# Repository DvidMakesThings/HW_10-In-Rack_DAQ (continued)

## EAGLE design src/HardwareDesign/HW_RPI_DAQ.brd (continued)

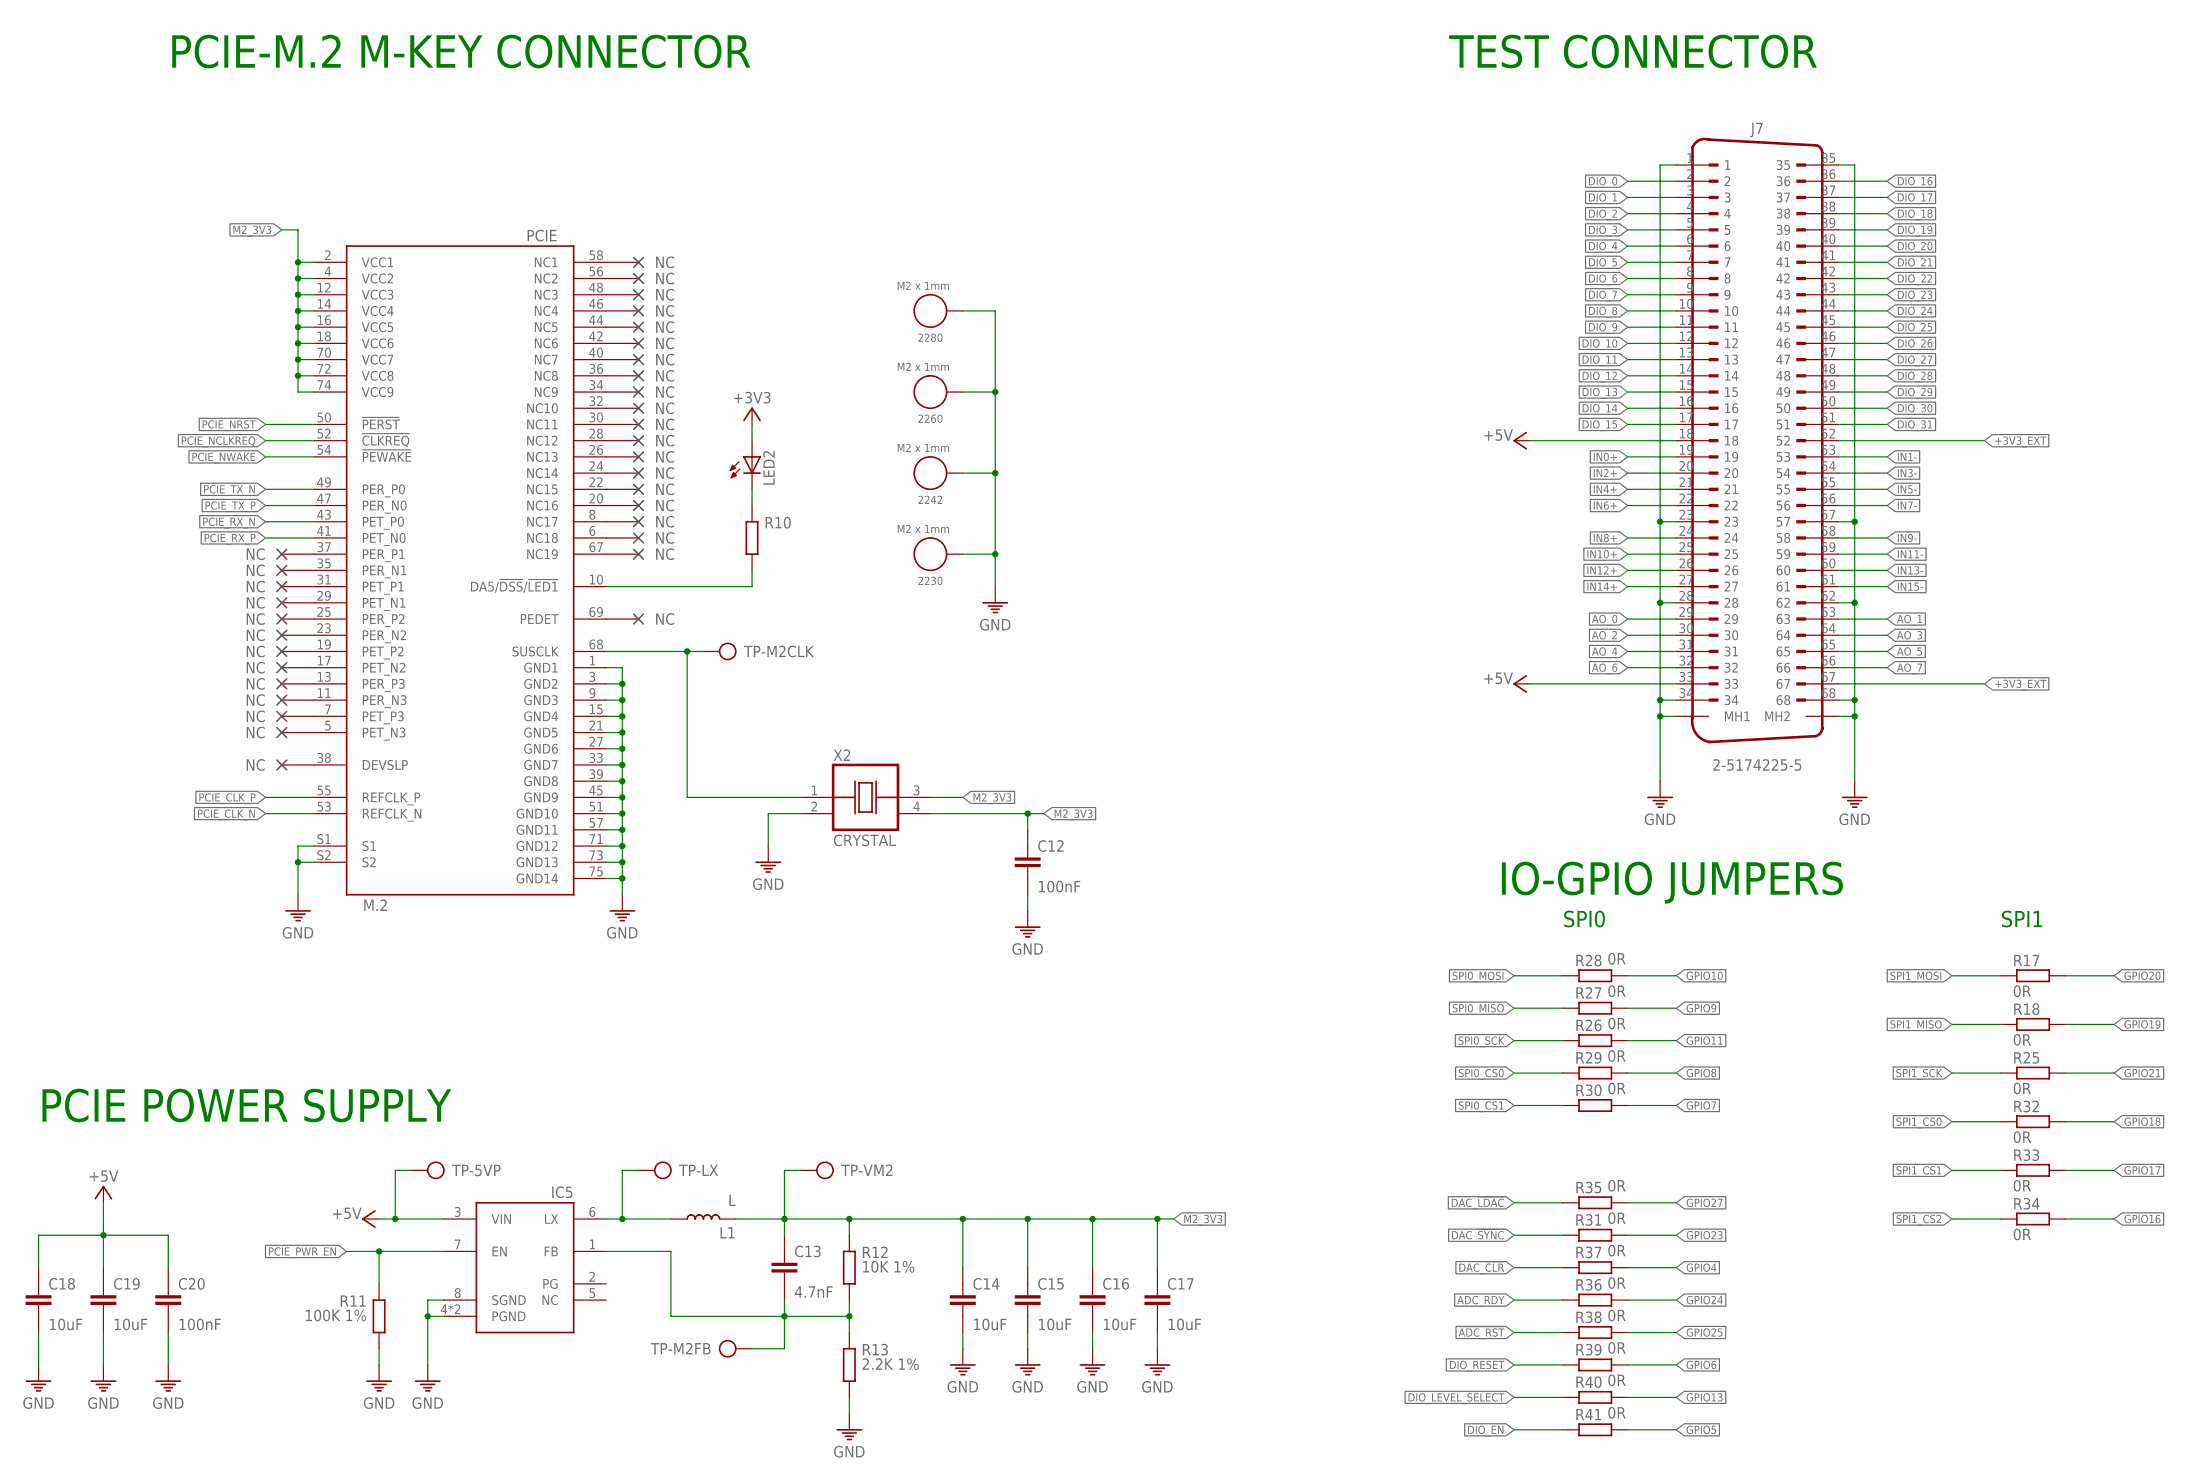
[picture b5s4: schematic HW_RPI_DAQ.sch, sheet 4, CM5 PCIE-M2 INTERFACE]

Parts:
2230, 2242, 2260, 2280: M2 x 1mm; WA-SMSI_9774010243
C12, C20: 100nF; 0402
C13: 4.7nF; 0402
C14, C15, C16, C17, C18, C19: 10uF; 0805
IC5: AP3441SHE-7B; SON50P201X201X56-9T90X170N
J7: 2-5174225-5
L1: L; SRR5228A
LED2: LEDCHIPLED_0805; CHIPLED_0805
PCIE: M.2
R10: R0402; 0402
R11: 100K 1%; 0402
R12: 10K 1%; 0402
R13: 2.2K 1%; 0402
R17, R18, R25, R26, R27, R28, R29, R30, R31, R32, R33, R34, R35, R36, R37, R38, R39, R40, R41: 0R; 0603
TP-5VP: TP
TP-LX: TP
TP-M2CLK, TP-M2FB: TP
TP-VM2: TP
X2: CRYSTAL; OSCCC500X320X130

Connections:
!ADC_RST: R38.1; also elsewhere on the board
+3V3: LED2.A; also elsewhere on the board
+3V3_EXT: J7.52, J7.67; also elsewhere on the board
+5V: C18.1, C19.1, C20.1, IC5.3 (VIN), J7.18, J7.33, TP-5VP.TP; also elsewhere on the board
ADC_RDY: R36.1; also elsewhere on the board
AO_0: J7.29; also elsewhere on the board
AO_1: J7.63; also elsewhere on the board
AO_2: J7.30; also elsewhere on the board
AO_3: J7.64; also elsewhere on the board
AO_4: J7.31; also elsewhere on the board
AO_5: J7.65; also elsewhere on the board
AO_6: J7.32; also elsewhere on the board
AO_7: J7.66; also elsewhere on the board
DAC_!CLR: R37.1; also elsewhere on the board
DAC_!LDAC: R35.1; also elsewhere on the board
DAC_!SYNC: R31.1; also elsewhere on the board
DIO_0: J7.2; also elsewhere on the board
DIO_1: J7.3; also elsewhere on the board
DIO_2: J7.4; also elsewhere on the board
DIO_3: J7.5; also elsewhere on the board
DIO_4: J7.6; also elsewhere on the board
DIO_5: J7.7; also elsewhere on the board
DIO_6: J7.8; also elsewhere on the board
DIO_7: J7.9; also elsewhere on the board
DIO_8: J7.10; also elsewhere on the board
DIO_9: J7.11; also elsewhere on the board
DIO_10: J7.12; also elsewhere on the board
DIO_11: J7.13; also elsewhere on the board
DIO_12: J7.14; also elsewhere on the board
DIO_13: J7.15; also elsewhere on the board
DIO_14: J7.16; also elsewhere on the board
DIO_15: J7.17; also elsewhere on the board
DIO_16: J7.36; also elsewhere on the board
DIO_17: J7.37; also elsewhere on the board
DIO_18: J7.38; also elsewhere on the board
DIO_19: J7.39; also elsewhere on the board
DIO_20: J7.40; also elsewhere on the board
DIO_21: J7.41; also elsewhere on the board
DIO_22: J7.42; also elsewhere on the board
DIO_23: J7.43; also elsewhere on the board
DIO_24: J7.44; also elsewhere on the board
DIO_25: J7.45; also elsewhere on the board
DIO_26: J7.46; also elsewhere on the board
DIO_27: J7.47; also elsewhere on the board
DIO_28: J7.48; also elsewhere on the board
DIO_29: J7.49; also elsewhere on the board
DIO_30: J7.50; also elsewhere on the board
DIO_31: J7.51; also elsewhere on the board
DIO_EN: R41.1; also elsewhere on the board
DIO_LEVEL_SELECT: R40.1; also elsewhere on the board
DIO_RESET: R39.1; also elsewhere on the board
GND: 2230.1, 2242.1, 2260.1, 2280.1, C12.2, C14.2, C15.2, C16.2, C17.2, C18.2, C19.2, C20.2, IC5.4 (PGND), IC5.8 (SGND), IC5.9 (PGND), J7.1, J7.23, J7.28, J7.34, J7.35, J7.57, J7.62, J7.68, J7.MH1, J7.MH2, PCIE.1 (GND1), PCIE.3 (GND2), PCIE.9 (GND3), PCIE.15 (GND4), PCIE.21 (GND5), PCIE.27 (GND6), PCIE.33 (GND7), PCIE.39 (GND8), PCIE.45 (GND9), PCIE.51 (GND10), PCIE.57 (GND11), PCIE.71 (GND12), PCIE.73 (GND13), PCIE.75 (GND14), PCIE.S1, PCIE.S2, R11.2, R13.2, X2.2 (VSS); also elsewhere on the board
GPIO4: R37.2; also elsewhere on the board
GPIO5: R41.2; also elsewhere on the board
GPIO6: R39.2; also elsewhere on the board
GPIO7: R30.2; also elsewhere on the board
GPIO8: R29.2; also elsewhere on the board
GPIO9: R27.2; also elsewhere on the board
GPIO10: R28.2; also elsewhere on the board
GPIO11: R26.2; also elsewhere on the board
GPIO13: R40.2; also elsewhere on the board
GPIO16: R34.2; also elsewhere on the board
GPIO17: R33.2; also elsewhere on the board
GPIO18: R32.2; also elsewhere on the board
GPIO19: R18.2; also elsewhere on the board
GPIO20: R17.2; also elsewhere on the board
GPIO21: R25.2; also elsewhere on the board
GPIO23: R31.2; also elsewhere on the board
GPIO24: R36.2; also elsewhere on the board
GPIO25: R38.2; also elsewhere on the board
GPIO27: R35.2; also elsewhere on the board
IN0+: J7.19; also elsewhere on the board
IN1-: J7.53; also elsewhere on the board
IN2+: J7.20; also elsewhere on the board
IN3-: J7.54; also elsewhere on the board
IN4+: J7.21; also elsewhere on the board
IN5-: J7.55; also elsewhere on the board
IN6+: J7.22; also elsewhere on the board
IN7-: J7.56; also elsewhere on the board
IN8+: J7.24; also elsewhere on the board
IN9-: J7.58; also elsewhere on the board
IN10+: J7.25; also elsewhere on the board
IN11-: J7.59; also elsewhere on the board
IN12+: J7.26; also elsewhere on the board
IN13-: J7.60; also elsewhere on the board
IN14+: J7.27; also elsewhere on the board
IN15-: J7.61; also elsewhere on the board
M2_3V3: C12.1, C13.1, C14.1, C15.1, C16.1, C17.1, L1.2, PCIE.2 (VCC1), PCIE.4 (VCC2), PCIE.12 (VCC3), PCIE.14 (VCC4), PCIE.16 (VCC5), PCIE.18 (VCC6), PCIE.70 (VCC7), PCIE.72 (VCC8), PCIE.74 (VCC9), R12.1, TP-VM2.TP, X2.3 (OUT), X2.4 (VDD)
unnamed: PCIE.10 (DA5/!DSS!/!LED1), R10.2
unnamed: LED2.C, R10.1
unnamed: IC5.6 (LX), L1.1, TP-LX.TP
unnamed: C13.2, IC5.1 (FB), R12.2, R13.1, TP-M2FB.TP
unnamed: PCIE.68 (SUSCLK), TP-M2CLK.TP, X2.1 (CON)
PCIE_CLK_N: PCIE.53 (REFCLK_N); also elsewhere on the board
PCIE_CLK_P: PCIE.55 (REFCLK_P); also elsewhere on the board
PCIE_NCLKREQ: PCIE.52 (!CLKREQ); also elsewhere on the board
PCIE_NRST: PCIE.50 (!PERST); also elsewhere on the board
PCIE_NWAKE: PCIE.54 (!PEWAKE); also elsewhere on the board
PCIE_PWR_EN: IC5.7 (EN), R11.1; also elsewhere on the board
PCIE_RX_N: PCIE.43 (PET_P0); also elsewhere on the board
PCIE_RX_P: PCIE.41 (PET_N0); also elsewhere on the board
PCIE_TX_N: PCIE.49 (PER_P0); also elsewhere on the board
PCIE_TX_P: PCIE.47 (PER_N0); also elsewhere on the board
SPI0_CS0: R29.1; also elsewhere on the board
SPI0_CS1: R30.1; also elsewhere on the board
SPI0_MISO: R27.1; also elsewhere on the board
SPI0_MOSI: R28.1; also elsewhere on the board
SPI0_SCK: R26.1; also elsewhere on the board
SPI1_CS0: R32.1; also elsewhere on the board
SPI1_CS1: R33.1; also elsewhere on the board
SPI1_CS2: R34.1; also elsewhere on the board
SPI1_MISO: R18.1; also elsewhere on the board
SPI1_MOSI: R17.1; also elsewhere on the board
SPI1_SCK: R25.1; also elsewhere on the board

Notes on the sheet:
PCIE-M.2 M-KEY CONNECTOR
PCIE POWER SUPPLY
TEST CONNECTOR
IO-GPIO JUMPERS
SPI0
SPI1

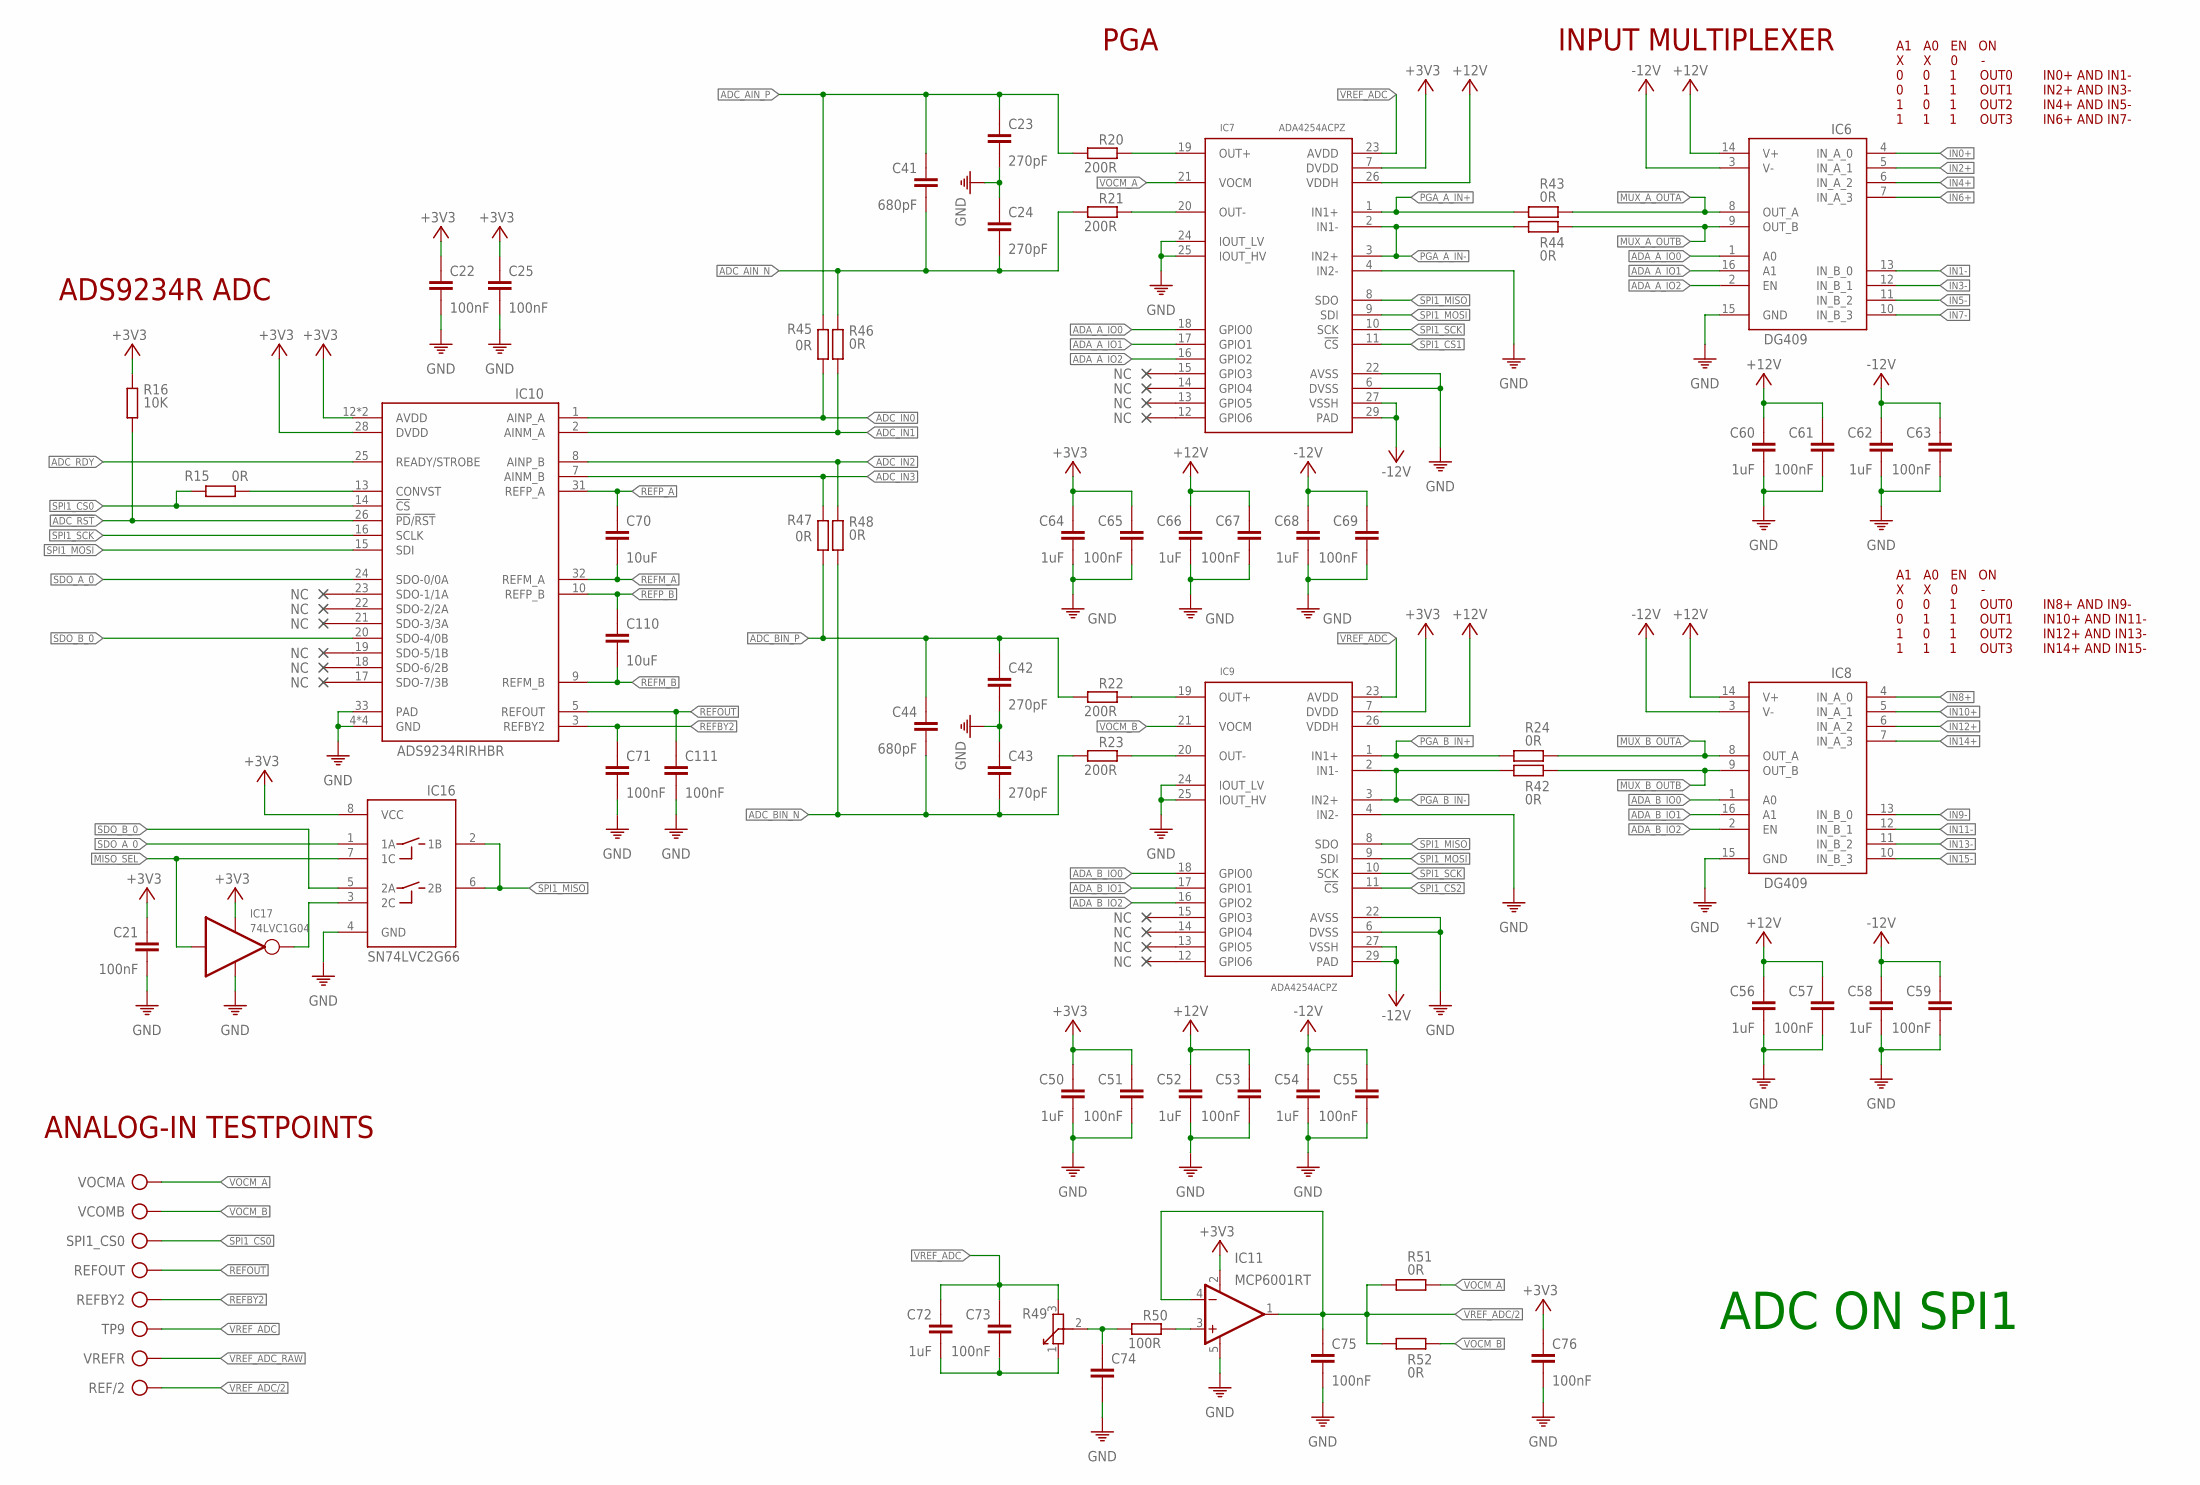
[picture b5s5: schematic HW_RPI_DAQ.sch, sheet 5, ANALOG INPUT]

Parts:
C21, C73: 100nF; 0603
C22, C25, C51, C53, C55, C57, C59, C61, C63, C65, C67, C69, C71, C75, C76, C111: 100nF; 0402
C23, C24, C42, C43: 270pF; 0402
C41, C44: 680pF; 0402
C50, C52, C54, C56, C58, C60, C62, C64, C66, C68, C72: 1uF; 0603
C70, C110: 10uF; 0603
C74: C0805; 0805
IC6, IC8: DG409; TSSOP2
IC7, IC9: ADA4254ACPZ; QFN50P500X500X75-29T314N
IC10: ADS9234RIRHBR; VQFN32-5X5
IC11: MCP6001RT; SOT23-5
IC16: SN74LVC2G66; SOP50P310X90-8N
IC17: 74LVC1G04; SOT95P280X145-5N
R15, R24, R42, R43, R44, R45, R46, R47, R48: 0R; 0402
R16: 10K; 0402
R20, R21, R22, R23: 200R; 0402
R49: R-TRIM; TC33X
R50: 100R; 0402
R51, R52: 0R; 0603
REF/2: TP
REFBY2: TP
REFOUT: TP
SPI1_CS0: TP
TP9: TP
VCOMB: TP
VOCMA: TP
VREFR: TP

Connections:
!ADC_RST: IC10.26 (!PD!/!RST), R16.2; also elsewhere on the board
!MISO_SEL: IC16.3 (2C), IC17.4 (OUT)
+3V3: C21.1, C22.1, C25.1, C50.1, C51.1, C64.1, C65.1, C76.1, IC7.7 (DVDD), IC9.7 (DVDD), IC10.12 (AVDD), IC10.28 (DVDD), IC10.29 (AVDD), IC11.2 (V+), IC16.8 (VCC), IC17.5 (V+), R16.1; also elsewhere on the board
+12V: C52.1, C53.1, C56.1, C57.1, C60.1, C61.1, C66.1, C67.1, IC6.14 (V+), IC7.26 (VDDH), IC8.14 (V+), IC9.26 (VDDH); also elsewhere on the board
-12V: C54.1, C55.1, C58.1, C59.1, C62.1, C63.1, C68.1, C69.1, IC6.3 (V-), IC7.27 (VSSH), IC7.29 (PAD), IC8.3 (V-), IC9.27 (VSSH), IC9.29 (PAD); also elsewhere on the board
ADA_A_IO0: IC6.1 (A0), IC7.18 (GPIO0)
ADA_A_IO1: IC6.16 (A1), IC7.17 (GPIO1)
ADA_A_IO2: IC6.2 (EN), IC7.16 (GPIO2)
ADA_B_IO0: IC8.1 (A0), IC9.18 (GPIO0)
ADA_B_IO1: IC8.16 (A1), IC9.17 (GPIO1)
ADA_B_IO2: IC8.2 (EN), IC9.16 (GPIO2)
ADC_AIN_N: C24.2, C41.2, R21.1, R46.1
ADC_AIN_P: C23.1, C41.1, R20.1, R45.2
ADC_BIN_N: C43.2, C44.2, R23.1, R48.2
ADC_BIN_P: C42.1, C44.1, R22.1, R47.1
ADC_IN0: IC10.1 (AINP_A), R45.1
ADC_IN1: IC10.2 (AINM_A), R46.2
ADC_IN2: IC10.8 (AINP_B), R48.1
ADC_IN3: IC10.7 (AINM_B), R47.2
ADC_RDY: IC10.25 (READY/STROBE); also elsewhere on the board
GND: C21.2, C22.2, C23.2, C24.1, C25.2, C42.2, C43.1, C50.2, C51.2, C52.2, C53.2, C54.2, C55.2, C56.2, C57.2, C58.2, C59.2, C60.2, C61.2, C62.2, C63.2, C64.2, C65.2, C66.2, C67.2, C68.2, C69.2, C71.2, C74.2, C75.2, C76.2, C111.2, IC6.15 (GND), IC7.4 (IN2-), IC7.6 (DVSS), IC7.22 (AVSS), IC7.24 (IOUT_LV), IC7.25 (IOUT_HV), IC8.15 (GND), IC9.4 (IN2-), IC9.6 (DVSS), IC9.22 (AVSS), IC9.24 (IOUT_LV), IC9.25 (IOUT_HV), IC10.4 (GND), IC10.11 (GND), IC10.27 (GND), IC10.30 (GND), IC10.33 (PAD), IC11.5 (V-), IC16.4 (GND), IC17.3 (V-); also elsewhere on the board
IN0+: IC6.4 (IN_A_0); also elsewhere on the board
IN1-: IC6.13 (IN_B_0); also elsewhere on the board
IN2+: IC6.5 (IN_A_1); also elsewhere on the board
IN3-: IC6.12 (IN_B_1); also elsewhere on the board
IN4+: IC6.6 (IN_A_2); also elsewhere on the board
IN5-: IC6.11 (IN_B_2); also elsewhere on the board
IN6+: IC6.7 (IN_A_3); also elsewhere on the board
IN7-: IC6.10 (IN_B_3); also elsewhere on the board
IN8+: IC8.4 (IN_A_0); also elsewhere on the board
IN9-: IC8.13 (IN_B_0); also elsewhere on the board
IN10+: IC8.5 (IN_A_1); also elsewhere on the board
IN11-: IC8.12 (IN_B_1); also elsewhere on the board
IN12+: IC8.6 (IN_A_2); also elsewhere on the board
IN13-: IC8.11 (IN_B_2); also elsewhere on the board
IN14+: IC8.7 (IN_A_3); also elsewhere on the board
IN15-: IC8.10 (IN_B_3); also elsewhere on the board
MISO_SEL: IC16.7 (1C), IC17.2 (IN)
MUX_A_OUTA: IC6.8 (OUT_A), R43.2
MUX_A_OUTB: IC6.9 (OUT_B), R44.1
MUX_B_OUTA: IC8.8 (OUT_A), R24.2
MUX_B_OUTB: IC8.9 (OUT_B), R42.1
unnamed: IC7.19 (OUT+), R20.2
unnamed: IC7.20 (OUT-), R21.2
unnamed: IC9.19 (OUT+), R22.2
unnamed: IC9.20 (OUT-), R23.2
unnamed: IC10.13 (CONVST), R15.2
unnamed: C72.2, C73.2, R49.1
unnamed: C74.1, R49.2, R50.1
unnamed: IC11.3 (+IN), R50.2
PGA_A_IN+: IC7.1 (IN1+), R43.1
PGA_A_IN-: IC7.2 (IN1-), IC7.3 (IN2+), R44.2
PGA_B_IN+: IC9.1 (IN1+), R24.1
PGA_B_IN-: IC9.2 (IN1-), IC9.3 (IN2+), R42.2
REFBY2: C71.1, IC10.3 (REFBY2), REFBY2.TP
REFM_A: C70.2, IC10.32 (REFM_A)
REFM_B: C110.2, IC10.9 (REFM_B)
REFOUT: C111.1, IC10.5 (REFOUT), REFOUT.TP
REFP_A: C70.1, IC10.31 (REFP_A)
REFP_B: C110.1, IC10.10 (REFP_B)
SDO_A_0: IC10.24 (SDO-0/0A), IC16.1 (1A)
SDO_B_0: IC10.20 (SDO-4/0B), IC16.5 (2A)
SPI1_CS0: IC10.14 (!CS), R15.1, SPI1_CS0.TP; also elsewhere on the board
SPI1_CS1: IC7.11 (!CS); also elsewhere on the board
SPI1_CS2: IC9.11 (!CS); also elsewhere on the board
SPI1_MISO: IC7.8 (SDO), IC9.8 (SDO), IC16.2 (1B), IC16.6 (2B); also elsewhere on the board
SPI1_MOSI: IC7.9 (SDI), IC9.9 (SDI), IC10.15 (SDI); also elsewhere on the board
SPI1_SCK: IC7.10 (SCK), IC9.10 (SCK), IC10.16 (SCLK); also elsewhere on the board
VOCM_A: IC7.21 (VOCM), R51.2, VOCMA.TP
VOCM_B: IC9.21 (VOCM), R52.1, VCOMB.TP
VREF_ADC: C72.1, C73.1, IC7.23 (AVDD), IC9.23 (AVDD), R49.3, TP9.TP; also elsewhere on the board
VREF_ADC/2: C75.1, IC11.1 (OUT), IC11.4 (-IN), R51.1, R52.2, REF/2.TP
VREF_ADC_RAW: VREFR.TP; also elsewhere on the board

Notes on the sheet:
ADS9234R ADC
A1 A0 EN ON
X X 0 -
0 0 1 OUT0
0 1 1 OUT1
1 0 1 OUT2
1 1 1 OUT3
IN0+ AND IN1-
IN2+ AND IN3-
IN4+ AND IN5-
IN6+ AND IN7-
IN8+ AND IN9-
IN10+ AND IN11-
IN12+ AND IN13-
IN14+ AND IN15-
ANALOG-IN TESTPOINTS
PGA
INPUT MULTIPLEXER
ADC ON SPI1

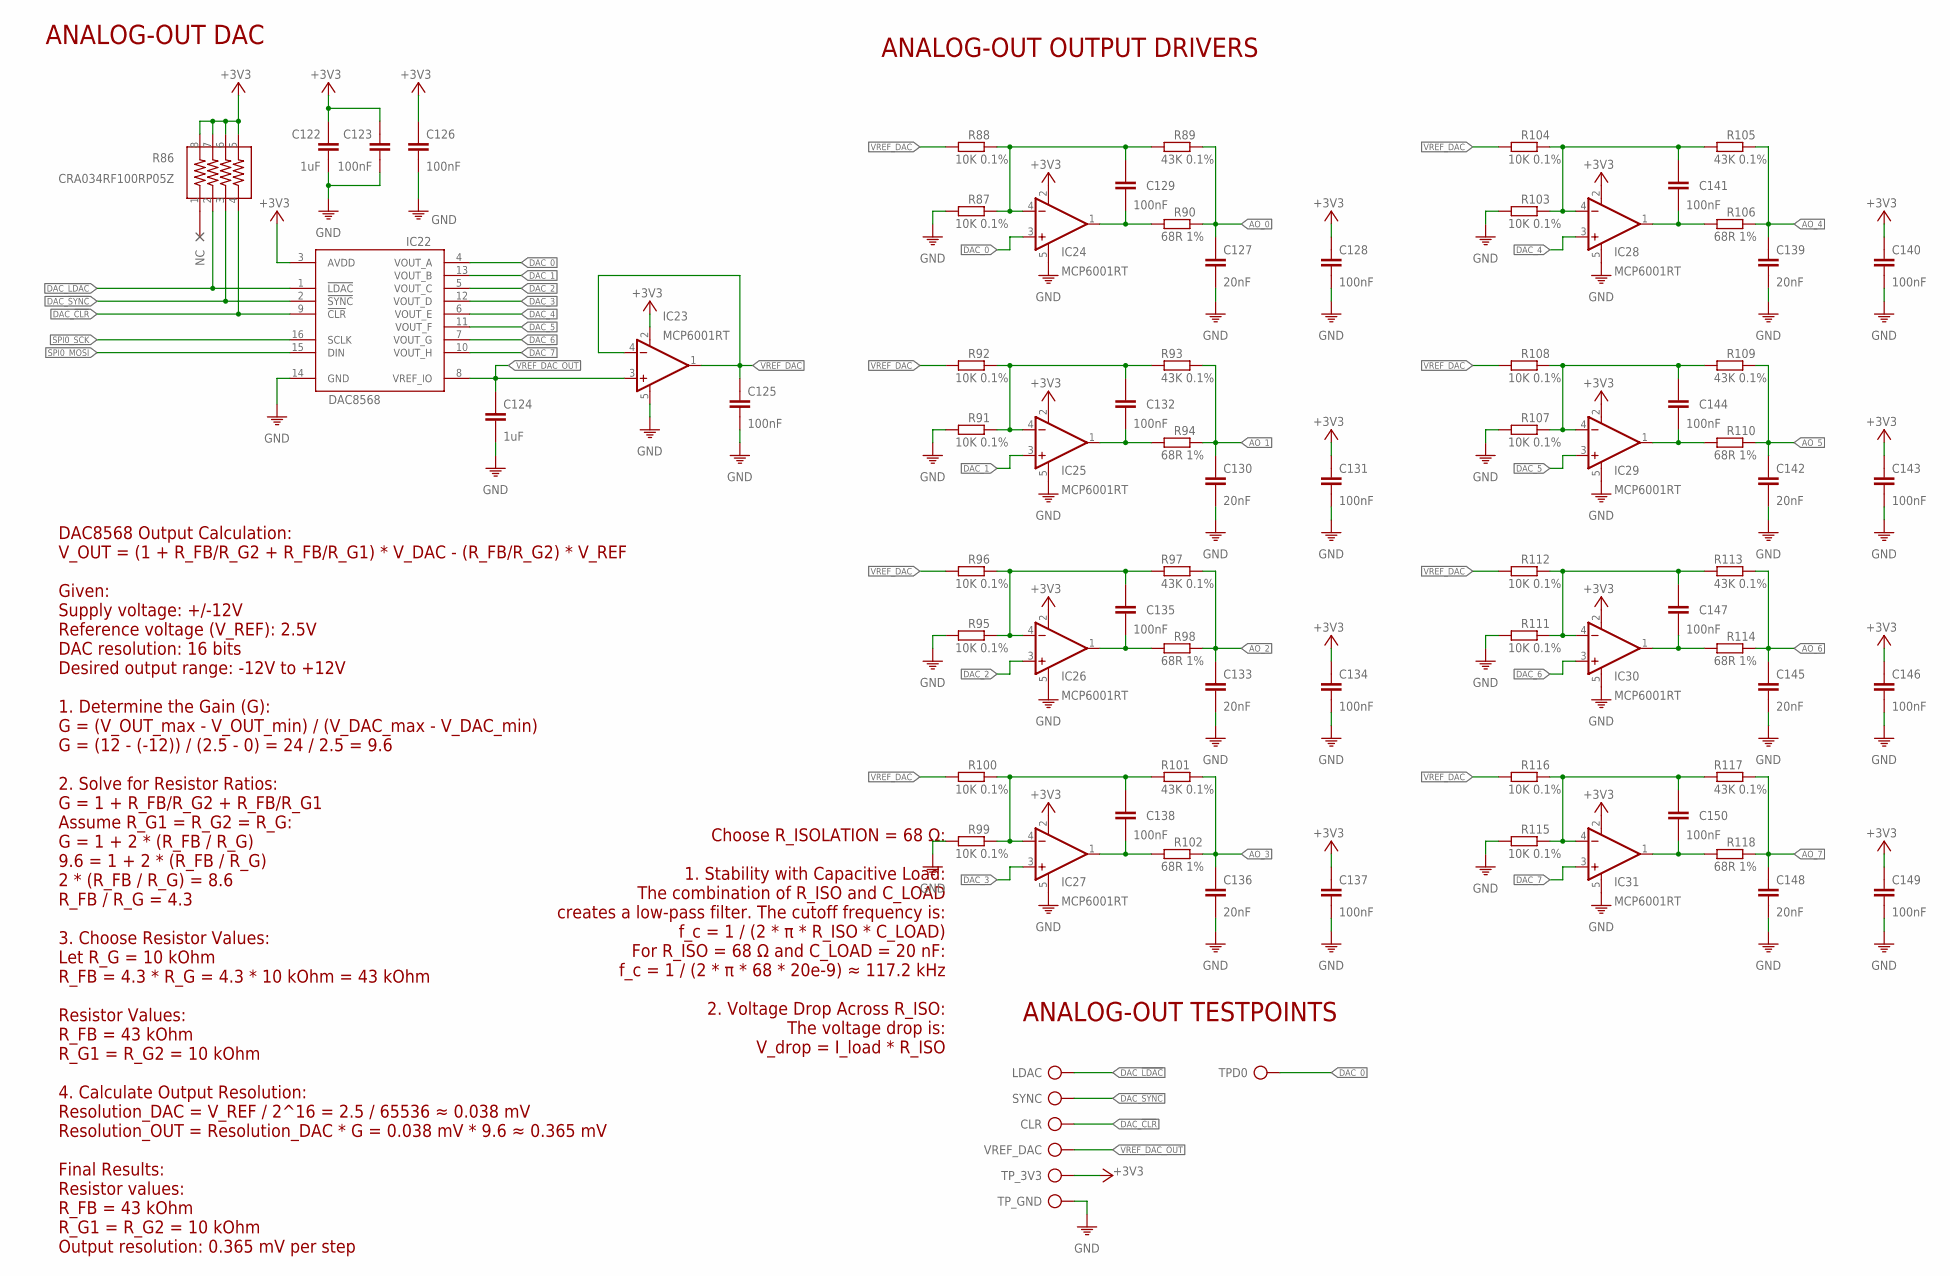
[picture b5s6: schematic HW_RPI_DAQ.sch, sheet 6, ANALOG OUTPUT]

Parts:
C122, C124: 1uF; 0603
C123: 100nF; 0603
C125, C126, C128, C129, C131, C132, C134, C135, C137, C138, C140, C141, C143, C144, C146, C147, C149, C150: 100nF; 0402
C127, C130, C133, C136, C139, C142, C145, C148: 20nF; 0402
CLR: TP
IC22: DAC8568; TSSOP16
IC23, IC24, IC25, IC26, IC27, IC28, IC29, IC30, IC31: MCP6001RT; SOT23-5
LDAC: TP
R86: CRA034RF100RP05Z; YC164-JR-0733RL
R87, R88, R91, R92, R95, R96, R99, R100, R103, R104, R107, R108, R111, R112, R115, R116: 10K 0.1%; 0402
R89, R93, R97, R101, R105, R109, R113, R117: 43K 0.1%; 0402
R90, R94, R98, R102, R106, R110, R114, R118: 68R 1%; 0402
SYNC: TP
TPD0: TP
TP_3V3: TP
TP_GND: TP
VREF_DAC: TP

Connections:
+3V3: C122.1, C123.1, C126.1, C128.1, C131.1, C134.1, C137.1, C140.1, C143.1, C146.1, C149.1, IC22.3 (AVDD), IC23.2 (V+), IC24.2 (V+), IC25.2 (V+), IC26.2 (V+), IC27.2 (V+), IC28.2 (V+), IC29.2 (V+), IC30.2 (V+), IC31.2 (V+), R86.5, R86.6, R86.7, R86.8, TP_3V3.TP; also elsewhere on the board
AO_0: C127.1, R89.2, R90.2; also elsewhere on the board
AO_1: C130.1, R93.2, R94.2; also elsewhere on the board
AO_2: C133.1, R97.2, R98.2; also elsewhere on the board
AO_3: C136.1, R101.2, R102.2; also elsewhere on the board
AO_4: C139.1, R105.2, R106.2; also elsewhere on the board
AO_5: C142.1, R109.2, R110.2; also elsewhere on the board
AO_6: C145.1, R113.2, R114.2; also elsewhere on the board
AO_7: C148.1, R117.2, R118.2; also elsewhere on the board
DAC_0: IC22.4 (VOUT_A), IC24.3 (+IN), TPD0.TP
DAC_1: IC22.13 (VOUT_B), IC25.3 (+IN)
DAC_2: IC22.5 (VOUT_C), IC26.3 (+IN)
DAC_3: IC22.12 (VOUT_D), IC27.3 (+IN)
DAC_4: IC22.6 (VOUT_E), IC28.3 (+IN)
DAC_5: IC22.11 (VOUT_F), IC29.3 (+IN)
DAC_6: IC22.7 (VOUT_G), IC30.3 (+IN)
DAC_7: IC22.10 (VOUT_H), IC31.3 (+IN)
DAC_!CLR: CLR.TP, IC22.9 (!CLR), R86.4; also elsewhere on the board
DAC_!LDAC: IC22.1 (!LDAC), LDAC.TP, R86.2; also elsewhere on the board
DAC_!SYNC: IC22.2 (!SYNC), R86.3, SYNC.TP; also elsewhere on the board
GND: C122.2, C123.2, C124.2, C125.2, C126.2, C127.2, C128.2, C130.2, C131.2, C133.2, C134.2, C136.2, C137.2, C139.2, C140.2, C142.2, C143.2, C145.2, C146.2, C148.2, C149.2, IC22.14 (GND), IC23.5 (V-), IC24.5 (V-), IC25.5 (V-), IC26.5 (V-), IC27.5 (V-), IC28.5 (V-), IC29.5 (V-), IC30.5 (V-), IC31.5 (V-), R87.1, R91.1, R95.1, R99.1, R103.1, R107.1, R111.1, R115.1, TP_GND.TP; also elsewhere on the board
unnamed: C129.2, IC24.1 (OUT), R90.1
unnamed: C129.1, IC24.4 (-IN), R87.2, R88.2, R89.1
unnamed: C132.1, IC25.4 (-IN), R91.2, R92.2, R93.1
unnamed: C132.2, IC25.1 (OUT), R94.1
unnamed: C135.1, IC26.4 (-IN), R95.2, R96.2, R97.1
unnamed: C135.2, IC26.1 (OUT), R98.1
unnamed: C138.1, IC27.4 (-IN), R99.2, R100.2, R101.1
unnamed: C138.2, IC27.1 (OUT), R102.1
unnamed: C141.1, IC28.4 (-IN), R103.2, R104.2, R105.1
unnamed: C141.2, IC28.1 (OUT), R106.1
unnamed: C144.1, IC29.4 (-IN), R107.2, R108.2, R109.1
unnamed: C144.2, IC29.1 (OUT), R110.1
unnamed: C147.1, IC30.4 (-IN), R111.2, R112.2, R113.1
unnamed: C147.2, IC30.1 (OUT), R114.1
unnamed: C150.1, IC31.4 (-IN), R115.2, R116.2, R117.1
unnamed: C150.2, IC31.1 (OUT), R118.1
SPI0_MOSI: IC22.15 (DIN); also elsewhere on the board
SPI0_SCK: IC22.16 (SCLK); also elsewhere on the board
VREF_DAC: C125.1, IC23.1 (OUT), IC23.4 (-IN), R88.1, R92.1, R96.1, R100.1, R104.1, R108.1, R112.1, R116.1
VREF_DAC_OUT: C124.1, IC22.8 (VREF_IO), IC23.3 (+IN), VREF_DAC.TP

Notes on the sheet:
DAC8568 Output Calculation: V_OUT = (1 + R_FB/R_G2 + R_FB/R_G1) * V_DAC - (R_FB/R_G2) * V_REF Given: Supply voltage: +/-12V Reference voltage (V_REF): 2.5V DAC resolution: 16 bits Desired output range: -12V to +12V 1. Determine the Gain (G): G = (V_OUT_max - V_OUT_min) / (V_DAC_max - V_DAC_min) G =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
Choose R_ISOLATION = 68 Ω: 1. Stability with Capacitive Load: The combination of R_ISO and C_LOAD creates a low-pass filter. The cutoff frequency is: f_c = 1 / (2 * π * R_ISO * C_LOAD) For R_ISO = 68 Ω and C_LOAD = 20 nF: f_c = 1 / (2 * π * 68 * 20e-9) ≈ 117.2 kHz 2. Voltage Drop Across R_ISO: The 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
ANALOG-OUT TESTPOINTS
ANALOG-OUT DAC
ANALOG-OUT OUTPUT DRIVERS
